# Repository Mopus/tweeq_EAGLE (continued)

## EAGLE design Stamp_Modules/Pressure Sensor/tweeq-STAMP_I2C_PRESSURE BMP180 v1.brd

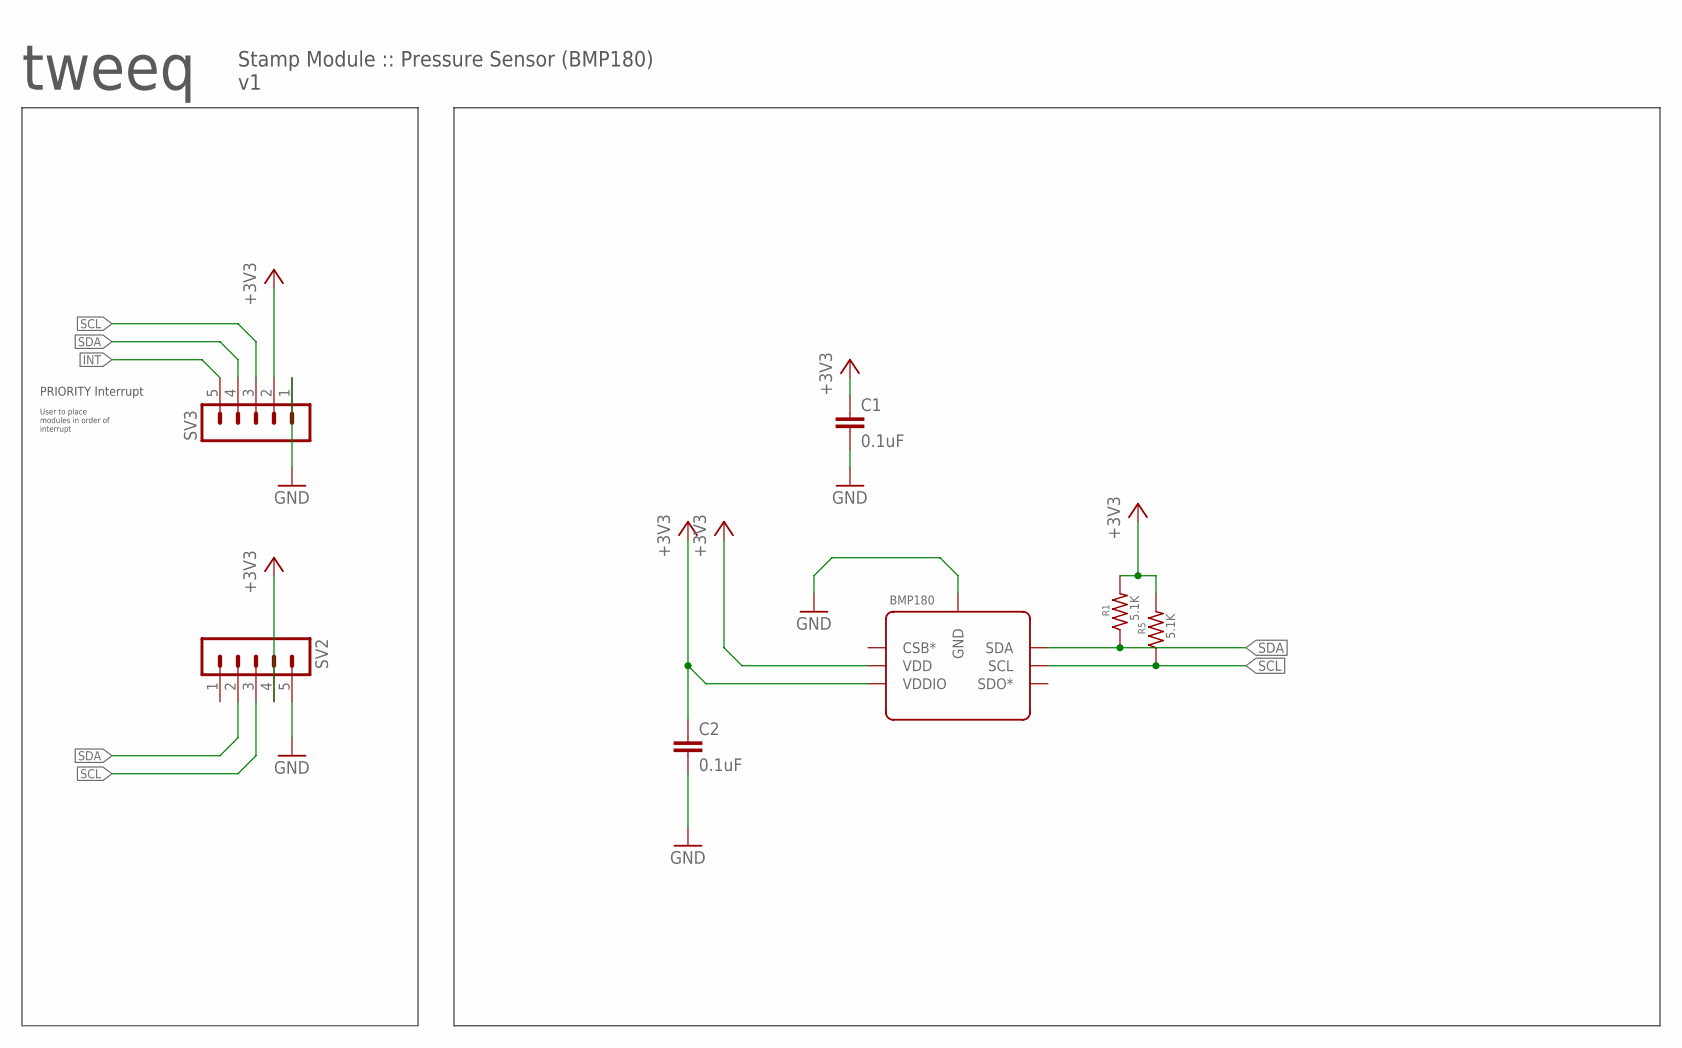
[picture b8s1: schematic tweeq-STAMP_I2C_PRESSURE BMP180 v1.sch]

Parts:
BMP180: BMP180; LGA-7PIN
C1, C2: 0.1uF; C0402K
R1, R5: 5.1K; R0402
SV2, SV3: M05-1STAMP; 1X05-1.5MM-STAMP

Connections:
+3V3: BMP180.2 (VDD), BMP180.3 (VDDIO), C1.1, C2.1, R1.2, R5.2, SV2.4, SV3.2
GND: BMP180.7 (GND), C1.2, C2.2, SV2.5, SV3.1
INT: SV3.5
SCL: BMP180.5 (SCL), R5.1, SV2.3, SV3.3
SDA: BMP180.6 (SDA), R1.1, SV2.2, SV3.4

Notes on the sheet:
tweeq
Stamp Module :: Pressure Sensor (BMP180) v1
PRIORITY Interrupt
User to place modules in order of interrupt

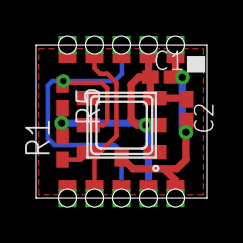
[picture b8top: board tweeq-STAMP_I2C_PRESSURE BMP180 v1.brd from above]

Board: 2 copper layers, 9.5 x 8.5 mm, 8 parts (1 on the bottom side), 4 nets.

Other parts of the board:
U$1: TWEEQ-LOGO-S
